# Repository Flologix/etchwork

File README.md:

# Etchwork

```text
      ┌────────────────────────────────────────────────────────────────────────┐
      │ ○                                                                      │
  ●───┤  ███████╗████████╗ ██████╗██╗  ██╗██╗    ██╗ ██████╗ ██████╗ ██╗  ██╗  ├───●
      │  ██╔════╝╚══██╔══╝██╔════╝██║  ██║██║    ██║██╔═══██╗██╔══██╗██║ ██╔╝  │
  ●───┤  █████╗     ██║   ██║     ███████║██║ █╗ ██║██║   ██║██████╔╝█████╔╝   ├───●
      │  ██╔══╝     ██║   ██║     ██╔══██║██║███╗██║██║   ██║██╔══██╗██╔═██╗   │
  ●───┤  ███████╗   ██║   ╚██████╗██║  ██║╚███╔███╔╝╚██████╔╝██║  ██║██║  ██╗  ├───●
      │  ╚══════╝   ╚═╝    ╚═════╝╚═╝  ╚═╝ ╚══╝╚══╝  ╚═════╝ ╚═╝  ╚═╝╚═╝  ╚═╝  │
  ●───┤                                                                        ├───●
      └────────────────────────────────────────────────────────────────────────┘
                    text in  ·  routed, DRC-clean KiCad boards out
```

A PCB design toolkit for AI coding agents. Write a sentence about what you need, and the engine produces a routed, DRC-clean, fab-ready KiCad board with Gerbers. It runs as an MCP server in Docker.

## Requirements

- **Linux** (macOS untested)
- **Docker** version 28 or later
- **git** and **python3**
- For Claude Code: the `claude` CLI

## Quick start (Claude Code)

**1. Install once.** Clone the repo, put `etchwork` on your `PATH`, and build the engine image.
The first build takes a few minutes.

```bash
git clone https://github.com/FlologixAI/etchwork.git ~/etchwork
mkdir -p ~/.local/bin && ln -s ~/etchwork/etchwork ~/.local/bin/etchwork
etchwork build
```

(If `etchwork` isn't found afterwards, open a new terminal: `~/.local/bin` must be on your `PATH`.)

**2. Set up a project folder.** Do this once for every new board.

```bash
mkdir ~/my-board && cd ~/my-board
etchwork init .
```

`init` picks your agent itself and prints which one it chose. If several are installed it asks;
pick Claude Code, or pass `--client claude-code`. It writes three things into the folder:
`.mcp.json` (how Claude Code starts the engine), the `/etchwork` skill, and a setting that
pre-approves the engine's tools.

**3. Design.** Start Claude Code in that folder. The first time, it asks whether to trust the
`etchwork` server: approve it. `/mcp` should then list `etchwork` as connected.

```bash
claude
```

```
/etchwork design a USB-C powered LED blinker using an ATtiny85, with a 6-pin ISP header
```

Say what matters to you: size limits, connectors, power, and parts you insist on. Approve the file
writes Claude Code asks about (`board.py`, `expected.netlist.toml`, `README.md`). A run takes
from minutes to about an hour, and ends when the agent reports **DONE**.

**4. What you get**, in the project folder:

| File | What it is |
|---|---|
| `board.kicad_pcb` | The board; open it in KiCad |
| `board.kicad_sch`, `board-schematic.pdf` | A schematic drawn from `board.py`, for reading and review |
| `gerbers/` | Fabrication files; zip them and upload to your fab |
| `board.py`, `board.net` | The circuit as a SKiDL script, and its netlist |
| `README.md` | What the board is, its parts, and its trace widths |

Read the **nets awaiting your decision** in the agent's final answer: they are the calls it left
to you.

The schematic is a reference drawing, generated from `board.py` and checked to match it. Change
the circuit through the agent, not the schematic, and don't use KiCad's "Update PCB from
Schematic" on an Etchwork project: KiCad doesn't know the schematic and board belong together, and
it can rewrite the routed board. Some boards (e.g. with multi-unit parts like op-amps) come without
a schematic, when the generator can't draw them correctly; `README.md` then says so, and why.

**5. Change it** by asking in the same session, e.g. "make the board smaller" or "add another
LED". Changes go through `board.py`, and the board is re-laid out and re-checked. If you edited
the board in KiCad yourself, the agent asks before replacing your layout.

After pulling a new version of Etchwork, run `etchwork build` again, then `etchwork init .` in
each project that should use the new engine.

## Other clients

Pass `--client codex`, `--client flai` or `--client marv` to `etchwork init`, or leave `--client` out and it
picks the agent itself: the one whose config the folder already has, else the only supported
agent installed, else it asks. See `docs/clients.md` for details.

## Where data goes

The engine container runs with no network. Your design files go only to your AI client's model provider—never anywhere else.

The engine keeps a local log of its tool calls in `.etchwork/events.jsonl` in the project folder:
which tool ran, how long it took, whether it passed, and DRC counts. It does not hold your
circuit, and it never leaves your machine unless you send it. Set `CIRCUIT_EVENTS=0` in the
engine's environment to turn it off, and add `.etchwork/` to `.gitignore` if you don't want it
committed.

## The isolated runner

For self-hosted, unattended production jobs, build a runner image that includes the engine and an agent:

```bash
./etchwork runner build --agent-bin <path to a Linux flai binary>
```

The runner's agent is currently a Linux flai binary — `--agent-bin` doesn't yet
take another agent. This prints `ENGINE=`, `EGRESS=` and `RUNNER=` image tags.
Then run a job:

```bash
ETCHWORK_EGRESS_IMAGE=<EGRESS> OPENROUTER_API_KEY=<key> ./etchwork job <RUNNER> <job dir>
```

`<job dir>/prompt.txt` holds the prompt; outputs land in `<job dir>.out/`, never
inside `<job dir>` itself. There is no REST API or status endpoint — this is a
one-shot container, run to completion (or `--probes`, which runs the isolation
probes instead of a real job).

## Status

**v0.2 pilot**: simple 2-layer boards on JLCPCB defaults.

**Guaranteed:**
- the board passed KiCad DRC, re-run by the packaging step on the delivered board under the project's design rules
- all nets are connected
- the pours are filled
- the Gerbers are current
- the named pin functions (MOSI, SCK, SDA…) are wired to pins that carry them

**Not guaranteed:**
- that the circuit works as intended
- part choices and availability
- thermal and electrical margins
- anything the prompt didn't say

[CONTRACT](contract/README.md) measures how often delivered boards meet the
requirements a prompt implied, the first slice of "not guaranteed".

## Licence

MIT; see [LICENSE](LICENSE). Contributions are welcome: see [CONTRIBUTING](CONTRIBUTING.md).

The engine image built by `etchwork build` bundles third-party software under its own licences,
notably KiCad and Freerouting (both GPL-3.0). [NOTICE](NOTICE) lists them and records where this
code came from.

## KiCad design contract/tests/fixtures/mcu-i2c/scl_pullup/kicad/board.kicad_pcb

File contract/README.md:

# CONTRACT

A requirement-conformance benchmark for agent-designed boards. Etchwork
guarantees a delivered board is DRC-clean, connected, poured and fab-ready; it
does not guarantee the circuit does what the prompt asked. CONTRACT measures
the first slice of that gap: **does the delivered board satisfy the
requirements the prompt implied?**

Design: `docs/superpowers/specs/2026-09-27-contract-benchmark-design.md`.

## Grading a board

```sh
./etchwork build                                      # once: the engine image
./etchwork contract score keyfob-base <job dir>.out   # or any dir with kicad/ + source/
```

`<board dir>` is a run's output: either it holds `deliverable.zip` (what
`etchwork job` writes), or it is an unpacked `kicad/*.kicad_pcb` +
`source/*.net` tree. The result goes to `contract-result.json` in the current
directory (`--out` to change it). It is never written into the board dir,
whose `result.json` belongs to the job.

Exit status: 0 when the board was graded (pass or fail, including a
non-delivery); 2 on a usage error (bad arguments); 3 on a harness error (an
unreadable task, a board that could not be unpacked or dumped, a clause that
could not be graded, or a result file that could not be written). Whenever a
task loaded, exit 3 still writes the result file if it can.

## The result

Each clause is one of:

- `pass` / `fail`: graded, with `detail` and `measured` saying what was found
  ("outline is 38.10 x 23.00 mm", not just "fail").
- `not_delivered`: no board came out of the run. This is a **strict failure**,
  never excluded from a denominator.
- `error`: the harness could not grade it (a crashed dump, a checker bug, a
  task naming a checker that does not exist). Listed under `harness_errors`,
  and never counted as a clause failure.

`strict_pass` is three-state:

- `true`: every clause passed.
- `false`: at least one clause is `fail` or `not_delivered`.
- `null`: no clause failed, but at least one is `error`, so the run has no
  verdict. A run the harness could not read at all is `null` too.

Consumers **exclude `strict_pass: null` runs from the strict-rate denominator**
and report them under harness integrity: a harness fault is never counted as
the agent's failure, nor as its success.

Three numbers are reported together and **never collapsed**:

- **Strict pass rate**: the fraction of runs passing every clause, over the
  runs with a verdict (`strict_pass` not `null`). The headline number.
- **Clause satisfaction rate**: per clause, the fraction of runs passing.
- **Harness integrity**: the fraction of runs with `graded: true`.

There is no composite or mean-of-clauses score, and there never will be.
Clauses are not equally weighted, and a composite invites the indefensible claim
that a board is "87% correct". Every published number states N, the number of
runs (default 5), because the same agent does not produce the same board twice.

## Tasks

`tasks/<name>/` holds `prompt.md` (handed to the agent), `contract.toml` (held
out, never shown to the agent) and `provenance.md` (source, derivation,
supplied-vs-withheld numbers, dropped clauses). The prompt carries intent; the
contract carries numbers. Every clause is a range or a relation, never a
comparison with a reference design.

`contract.toml` declares `[parts.<alias>]` allowlists (regexes over `ref`,
`lib_id`, `value`, a `pads` count list, and `with_pins`: words at least one of
the part's pins, connected or not, must carry) and `[nets.<alias>]` function
matchers (`words` matched against pin words,
optionally limited to a `part`; or `pins`, pad numbers on a `part`, for a
connector whose pins are named only `Pin_n`).
Clauses name a checker and pass aliases as arguments.

| Task | Board | Tests |
|---|---|---|
| `keyfob-base` | two-button 433 MHz coin-cell keyfob | parts, encoder support circuit, envelope |
| `usbc-ldo` | USB-C in, 3.3 V / 500 mA LDO out | CC pull-downs, regulator rating, regulator caps |
| `usb-serial` | USB-C to 5 V serial adapter (CH340C) | USB data pair, TX/RX to the right header pins, auto-reset, bridge caps |
| `relay-driver` | 3.3 V logic switching a 12 V relay via an N-MOSFET | flyback diode and its orientation, gate pull-down and series resistor, logic-level MOSFET |
| `mcu-i2c` | ATmega328P at 3.3 V / 8 MHz reading a BME280 over I2C | a cap at every supply pin, AVCC, reset and I2C pull-ups, crystal load caps, sensor strap pins |

A pad's words are the words of its pin names. Only when the pad has no pin
names do the words of its net's name count instead, and a KiCad
auto-generated net name (`Net-(...)`, `unconnected-(...)`) contributes no
words at all: `Net-(D2-A)` names a designator, not a data input D2.

## Checkers

| Checker | Checks |
|---|---|
| `outline_within` | outline bounding box within W x H (+tol), either orientation |
| `part_present` | at least `count` parts match an allowlist |
| `series_part_between` | a two-terminal part of a designator kind, value in range, between two nets; with one net, in series (its shared node carries no other parts) |
| `decoupling_near` | a cap >= N farads across supply and ground, within N mm of a supply pin; with `each`, of every supply pin |
| `net_connects` | two nets meet; or every matching part reaches a net (optionally each a distinct one) |
| `no_short` | two nets are distinct |
| `diode_across` | a diode with its cathode on one net and its anode on another, by pin name; a diode with both ends on one net is not across; any reversed diode fails, even beside a right one (it shorts the supply), and names the ref; unnamed fails |

A checker is a pure function `(board, **args) -> Result` over `contract/board.py`.
It never touches pcbnew; the one pcbnew dump runs inside the engine image
(`contract/dump.py`). Register new checkers in `checkers/__init__.py`.

## Testing CONTRACT itself

```sh
python3 -m pytest contract/tests -q     # host: pure tests; pcbnew tests skip
./etchwork contract test                # engine image: everything
./etchwork contract fixtures            # regenerate the mutation fixtures
```

There is no golden reference board (the seed design has no licence, so none
is vendored). Trust in the grader rests on **mutation fixtures**: a clean board
that passes every clause, and one mutant per clause that fails that clause and
no other. Adversarial variants, named `<clause>--<case>`, each script one way
the grader could be fooled into a false pass (a capacitor beside the
transmitter rather than the encoder, a resistor touching the LED's net but not
in series with it, a connector in place of a switch, an auto-named net) and
must likewise fail their named clause and no other.

## Stated limits

CONTRACT measures conformance of a delivered board to a written clause list
derived from one real design, checked statically. It does not measure that the
board works. It does not simulate. It does not cover RF. It does not check
firmware, part availability, thermal or electrical margin, or EMC. A board that
passes every clause is not a validated product, and a clause that fails may
indicate a defensible alternative design rather than an error.

Net clauses find pins by function: by the pin names in the netlist's library
symbols or the pads' pin functions, or, for a pad whose pin has no name, by
its net's name (never a KiCad auto-generated one). A part with neither named
pins nor meaningfully named nets cannot be identified, and its net clauses
fail.

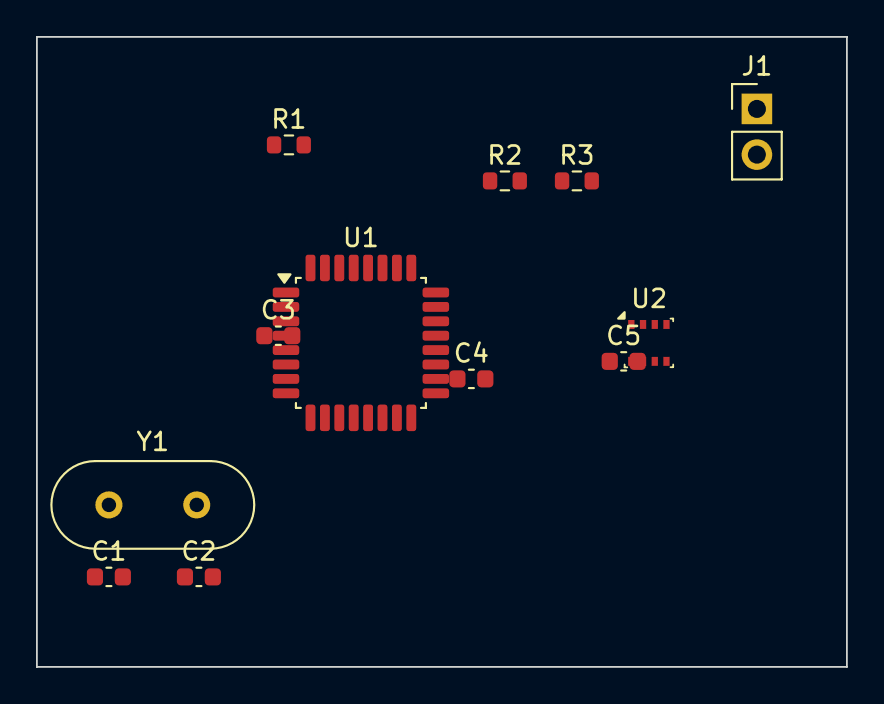
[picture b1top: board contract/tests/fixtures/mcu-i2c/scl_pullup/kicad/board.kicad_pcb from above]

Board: 2 copper layers, 45.0 x 35.0 mm, 12 parts (0 on the bottom side), 7 nets, no tracks yet.

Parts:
C1, C2: 22p; C_0603_1608Metric
C3, C4, C5: 100n; C_0603_1608Metric
J1: Conn_01x02; PinHeader_1x02_P2.54mm_Vertical
R1: 10k; R_0603_1608Metric
R2: 4.7k; R_0603_1608Metric
R3: 100; R_0603_1608Metric
U1: ATmega328P-AU; TQFP-32_7x7mm_P0.8mm
U2: BME280; Bosch_LGA-8_2.5x2.5mm_P0.65mm_ClockwisePinNumbering
Y1: 8MHz; Crystal_HC49-4H_Vertical

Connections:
+3V3: C3.1, C4.1, C5.1, J1.1, R1.2, R2.2, R3.2, U1.4 (VCC), U1.6 (VCC), U1.18 (AVCC), U2.2 (CSB), U2.6 (VDDIO), U2.8 (VDD)
GND: C1.2, C2.2, C3.2, C4.2, C5.2, J1.2, U1.3 (GND), U1.5 (GND), U1.21 (GND), U2.1 (GND), U2.5 (SDO), U2.7 (GND)
N_RST: R1.1, U1.29 (~RESET/PC6)
N_SCL: R3.1, U1.28 (SCL/PC5), U2.4 (SCK)
N_SDA: R2.1, U1.27 (SDA/PC4), U2.3 (SDI)
XT1: C1.1, U1.7 (XTAL1/PB6), Y1.1
XT2: C2.1, U1.8 (XTAL2/PB7), Y1.2

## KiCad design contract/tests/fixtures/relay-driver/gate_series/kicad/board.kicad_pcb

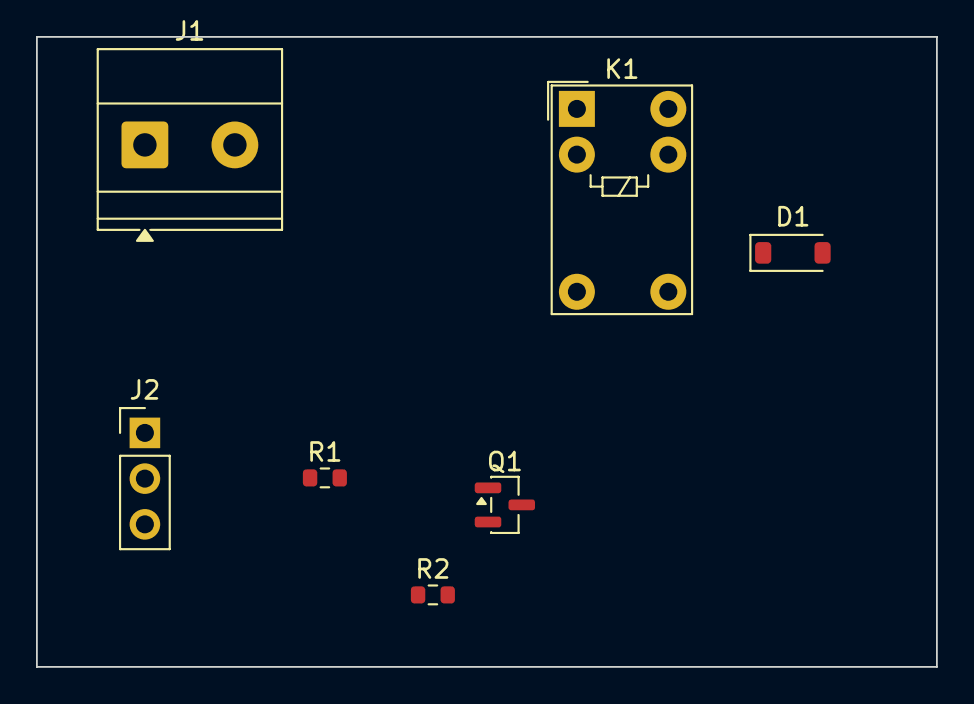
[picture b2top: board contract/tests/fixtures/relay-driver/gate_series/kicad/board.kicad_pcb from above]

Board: 2 copper layers, 50.0 x 35.0 mm, 7 parts (0 on the bottom side), 5 nets, no tracks yet.

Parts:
D1: 1N4148W; D_SOD-123
J1: Screw_Terminal_01x02; TerminalBlock_Phoenix_MKDS-1,5-2_1x02_P5.00mm_Horizontal
J2: Conn_01x03; PinHeader_1x03_P2.54mm_Vertical
K1: G5V-1; Relay_SPDT_Omron_G5V-1
Q1: AO3400A; SOT-23
R1: 10k; R_0603_1608Metric
R2: 100k; R_0603_1608Metric

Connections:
+12V: D1.1 (K), J1.1, K1.1
GND: J1.2, J2.1, Q1.2 (S), R2.2
N_DRAIN: D1.2 (A), K1.10, Q1.3 (D)
N_GATE: Q1.1 (G), R1.2, R2.1
N_SIG: J2.2, R1.1

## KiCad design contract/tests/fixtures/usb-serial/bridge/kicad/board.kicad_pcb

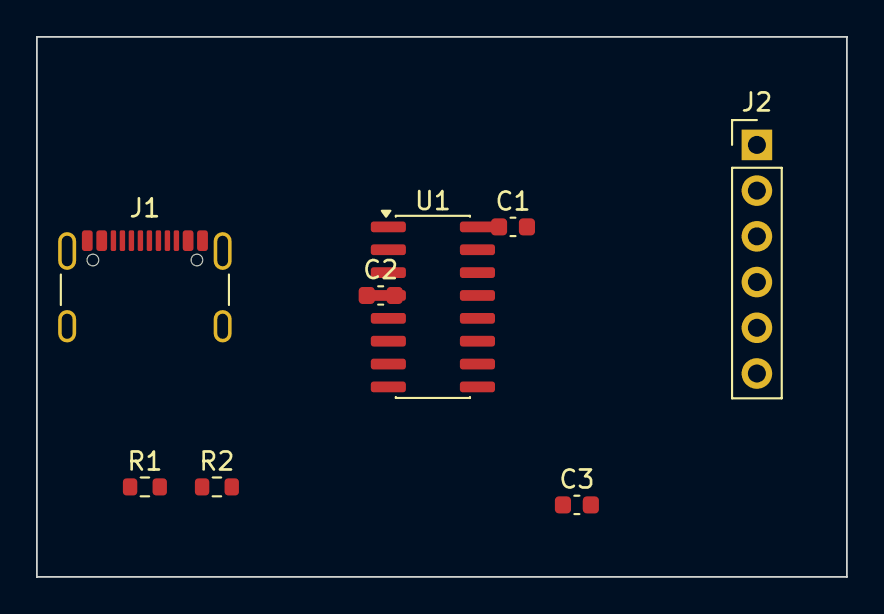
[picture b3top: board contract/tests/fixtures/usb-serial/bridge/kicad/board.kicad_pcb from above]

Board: 2 copper layers, 45.0 x 30.0 mm, 8 parts (0 on the bottom side), 11 nets, no tracks yet.

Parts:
C1, C2, C3: 100n; C_0603_1608Metric
J1: USB_C_Receptacle_USB2.0_16P; USB_C_Receptacle_GCT_USB4105-xx-A_16P_TopMnt_Horizontal
J2: Conn_01x06; PinHeader_1x06_P2.54mm_Vertical
R1, R2: 5.1k; R_0603_1608Metric
U1: CH340E; SOIC-16_3.9x9.9mm_P1.27mm

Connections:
CC1: J1.A5 (CC1), R1.1
CC2: J1.B5 (CC2), R2.1
D+: J1.A6 (D+), J1.B6 (D+), U1.5 (UD+)
D-: J1.A7 (D-), J1.B7 (D-), U1.6 (UD-)
GND: C1.2, C2.2, J1.A1 (GND), J1.A12 (GND), J1.B1 (GND), J1.B12 (GND), J1.SH (SHIELD), J2.1, R1.2, R2.2, U1.1 (GND)
N_DTR: C3.1, U1.13 (~DTR)
N_RST: C3.2, J2.6
N_RX: J2.5, U1.3 (RXD)
N_TX: J2.4, U1.2 (TXD)
N_V3: C2.1, U1.4 (V3)
VBUS: C1.1, J1.A4 (VBUS), J1.A9 (VBUS), J1.B4 (VBUS), J1.B9 (VBUS), J2.3, U1.16 (VCC)

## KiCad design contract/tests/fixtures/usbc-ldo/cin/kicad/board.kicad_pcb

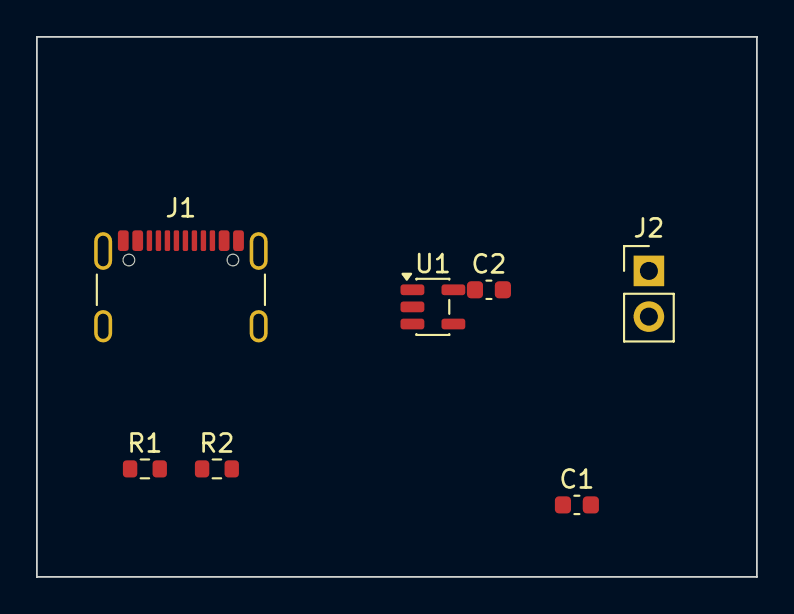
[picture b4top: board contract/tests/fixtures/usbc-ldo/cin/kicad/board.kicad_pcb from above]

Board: 2 copper layers, 40.0 x 30.0 mm, 7 parts (0 on the bottom side), 5 nets, no tracks yet.

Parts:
C1, C2: 1u; C_0603_1608Metric
J1: USB_C_Receptacle_USB2.0_16P; USB_C_Receptacle_GCT_USB4105-xx-A_16P_TopMnt_Horizontal
J2: Conn_01x02; PinHeader_1x02_P2.54mm_Vertical
R1, R2: 5.1k; R_0603_1608Metric
U1: AP2112K-3.3; SOT-23-5

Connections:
+3V3: C2.1, J2.1, U1.5 (VOUT)
CC1: J1.A5 (CC1), R1.1
CC2: J1.B5 (CC2), R2.1
GND: C1.1, C2.2, J1.A1 (GND), J1.A12 (GND), J1.B1 (GND), J1.B12 (GND), J1.SH (SHIELD), J2.2, R1.2, R2.2, U1.2 (GND)
VBUS: C1.2, J1.A4 (VBUS), J1.A9 (VBUS), J1.B4 (VBUS), J1.B9 (VBUS), U1.1 (VIN), U1.3 (EN)

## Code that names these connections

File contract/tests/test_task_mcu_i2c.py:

"""mcu-i2c: the task loads, withholds its numbers and strap pins, and its
crystal clauses pass a 4-pad crystal (design 2026-09-29-contract-tasks §4.4)."""
from pathlib import Path

import pytest

from contract import score
from contract.board import Footprint
from contract.checkers import REGISTRY
from contract.match import parse_value
from contract.tests.boards import fp, make, pad

TASK = Path(__file__).resolve().parents[1] / "tasks" / "mcu-i2c"
IDS = ["mcu", "sensor", "crystal", "mcu_decoupling", "avcc", "reset_pullup", "crystal_xtal1",
       "crystal_xtal2", "xtal1_load", "xtal2_load", "sda_pullup", "scl_pullup", "sda_wired",
       "scl_wired", "csb_high", "sda_scl_distinct", "xtal_distinct", "sdo_tied",
       "sensor_decoupling"]


def _clause(clause_id):
    return {c.id: c for c in score.load_task(TASK).clauses}[clause_id]


def _run(clause_id, board):
    c = _clause(clause_id)
    return REGISTRY[c.checker](board, **c.args)


def test_loads_every_clause_with_no_errors():
    t = score.load_task(TASK)
    assert [c.id for c in t.clauses] == IDS
    assert [c.error for c in t.clauses] == [None] * len(IDS)


def test_decoupling_clauses_ask_for_every_pin():
    assert _clause("mcu_decoupling").args["each"] is True
    assert _clause("sensor_decoupling").args["each"] is True


def test_prompt_withholds_the_numbers_and_strap_pins():
    prompt = (TASK / "prompt.md").read_text()
    for secret in ["22p", "pF", "100n", "nF", "10k", "4.7k", "4k7", "3 mm", "CSB", "SDO",
                   "pull", "AVCC"]:
        assert secret not in prompt, secret


@pytest.mark.parametrize("value, ok", [("8MHz", True), ("8 MHz", True), ("8.000MHz", True),
                                       ("8M", True), ("16MHz", False), ("18MHz", False),
                                       ("80MHz", False), ("8kHz", False)])
def test_crystal_allowlist(value, ok):
    part = Footprint("Y1", value, "Crystal:Crystal_HC49-4H_Vertical", (0.0, 0.0), 0.0, (), 2)
    assert _clause("crystal").args["part"].matches(part) is ok


@pytest.mark.parametrize("value, ok", [("ATmega328P-AU", True), ("ATmega328P-MU", True),
                                       ("ATmega328-PU", True), ("ATmega32U4-AU", False),
                                       ("ATmega168-AU", False),
                                       ("ATmega328PB-AU", False)])
def test_mcu_allowlist(value, ok):
    part = Footprint("U1", value, "Package_QFP:TQFP-32_7x7mm_P0.8mm", (0.0, 0.0), 0.0, (), 32)
    assert _clause("mcu").args["part"].matches(part) is ok


@pytest.mark.parametrize("load, pullup", [("22p", "4.7k"), ("22pF", "4k7"), ("18pF", "10k"),
                                          ("12p", "2.2K"), ("27pF", "1k")])
def test_common_value_spellings_fall_in_range(load, pullup):
    xl, pu = _clause("xtal1_load").args, _clause("sda_pullup").args
    assert xl["min"] <= parse_value(load) <= xl["max"]
    assert pu["min"] <= parse_value(pullup) <= pu["max"]


def test_four_pad_crystal_passes():
    # Y1 with grounded case pads 2 and 4: three nets on one part.
    board = make(
        footprints=[fp("U1", "ATmega328P-AU", pad_count=32),
                    fp("Y1", "8MHz", pad_count=4), fp("C1", "22p"), fp("C2", "22p")],
        pads=[pad("U1", 7, "XT1", names=["XTAL1/PB6"]), pad("U1", 8, "XT2", names=["XTAL2/PB7"]),
              pad("U1", 18, "+3V3", names=["AVCC"]), pad("U1", 5, "GND", names=["GND"]),
              pad("Y1", 1, "XT1"), pad("Y1", 2, "GND"), pad("Y1", 3, "XT2"), pad("Y1", 4, "GND"),
              pad("C1", 1, "XT1"), pad("C1", 2, "GND"), pad("C2", 1, "XT2"), pad("C2", 2, "GND")])
    for clause_id in ["crystal", "crystal_xtal1", "crystal_xtal2", "xtal1_load", "xtal2_load"]:
        result = _run(clause_id, board)
        assert result.passed, (clause_id, result.detail)


def test_csb_on_a_ferrite_isolated_sensor_rail_passes():
    # CSB follows the sensor's own supply, which sits behind a ferrite.
    board = make(
        footprints=[fp("U1", "BME280", pad_count=8), fp("L1", "BLM18")],
        pads=[pad("U1", 2, "VDD_S", names=["CSB"]), pad("U1", 6, "VDD_S", names=["VDDIO"]),
              pad("U1", 8, "VDD_S", names=["VDD"]), pad("L1", 1, "+3V3"),
              pad("L1", 2, "VDD_S")])
    result = _run("csb_high", board)
    assert result.passed, result.detail


def test_qfn_pins_named_pc4_pc5_are_sda_and_scl():
    # ATmega328P-M carries only PC4 / PC5 on pads 27 / 28.
    board = make(
        footprints=[fp("U1", "ATmega328P-MU", pad_count=33), fp("U2", "BME280", pad_count=8),
                    fp("R1", "4.7k"), fp("R2", "4.7k")],
        pads=[pad("U1", 4, "+3V3", names=["VCC"]), pad("U1", 18, "+3V3", names=["AVCC"]),
              pad("U1", 27, "N_SDA", names=["PC4"]), pad("U1", 28, "N_SCL", names=["PC5"]),
              pad("U2", 2, "+3V3", names=["CSB"]), pad("U2", 3, "N_SDA", names=["SDI"]), pad("U2", 4, "N_SCL", names=["SCK"]),
              pad("R1", 1, "N_SDA"), pad("R1", 2, "+3V3"),
              pad("R2", 1, "N_SCL"), pad("R2", 2, "+3V3")])
    for clause_id in ["sda_pullup", "scl_pullup", "sda_wired", "scl_wired", "sda_scl_distinct"]:
        result = _run(clause_id, board)
        assert result.passed, (clause_id, result.detail)
